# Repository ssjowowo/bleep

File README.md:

# Bleep

**A DIY touchscreen universal remote.** It's built around an ESP32-S3 on a main board of our own, with a 3.5″ IPS touch display, 14 physical keys, IR send and learn, haptics, and Home Assistant control over Wi-Fi. The case is 3D-printed and only 13 mm thick.

<p align="center">
  
  &nbsp;
  
</p>

## What it is

Most universal remotes either have a screen and few buttons, or lots of buttons and no screen. Bleep has both. The touchscreen shows activities, now-playing and smart-home controls. The keys you use without looking stay physical: a D-pad ring with OK, Back, Home, Mute, three app keys (YouTube, Netflix, Plex) and a volume rocker.

- **IR out**: two side-view 940 nm IR LEDs at the top end control TVs, receivers and boxes.
- **IR learning**: a 38 kHz receiver behind a small window under the screen copies codes from your old remotes.
- **Wi-Fi**: Home Assistant control of lights, scenes and media through the ESP32-S3.
- **Feel**: a coin vibration motor driven by a DRV2605L haptics driver.
- **Smart power**: lift-to-wake (accelerometer), wake on touch or any key, auto-brightness (light sensor), and a fuel gauge for an accurate battery percentage. Asleep it draws about 0.1–0.15 mA, so a charge lasts months.
- **USB-C** for charging and flashing.

The hardware is designed for all of this. The firmware's app and UI run today in an emulator (on the PC or in a browser) while the boards are being made; the ESP32-S3 port comes when they arrive. See [firmware/README.md](firmware/README.md).

The industrial design comes from a concept pack made in Claude Design (design **1b "Pebble"**, in `design/`). The brand (wordmark, logo lockup) comes from the Bleep brand book.

## Status

| Part | State |
|---|---|
| Main board v1 | **Ordered** from JLCPCB on 2026-10-08 (5 boards, 2 assembled). The design is locked: the files in `hardware/mainboard/` are the ones in production. |
| Enclosure | Ready to print. The back plate is flat, with room for a 4.0 × 50 × 85 mm Li-Po (405085) under the screen. |
| Display | BuyDisplay ER-TFT035IPS-6 + capacitive touch, **ordered** 2026-10-09. Its cable fold gets checked on the real panel before assembly. |
| Battery | **Ordered** 2026-10-09 (405085 planned; if the cell differs, set `BATT` in `layout.py` and rebuild the back plate). |
| Firmware | App and UI (C + LVGL 9) running in a PC/browser emulator with 32 scripted test scenarios; ESP-IDF port next. [firmware/](firmware/) |

## Hardware at a glance

| | |
|---|---|
| Size | 60.7 × 182.2 × 13.0 mm |
| MCU | ESP32-S3-WROOM-1-N8R2 (8 MB flash, 2 MB PSRAM), antenna at the right edge beside the D-pad |
| Display | 3.5″ IPS 320 × 480, ILI9488 on an 8-bit parallel bus (much faster than SPI), FT6236 capacitive touch |
| Keys | 14 tactile switches, each on its own wake-capable GPIO |
| IR | 2 × VSMB2948SL LEDs (≈ 125 mA peaks), IRM-H638T receiver for learning |
| Sensors | MMA8452Q accelerometer, LTR-303ALS light sensor, MAX17048 fuel gauge |
| Power | 1-cell Li-Po, TP4056 charger with load sharing, ME6211 3.3 V LDO |
| Board | 2 layers, 0.8 mm, 54 × 178 mm. JLCPCB assembles the top side; you solder the ESP32 module, battery and motor on the underside. |
| Case | PETG, two colours for the key labels (flush inlays), plus translucent blue PETG for the IR and sensor windows (two small separate prints); the board screwed to the front shell (4 × M2×4) and the back plate held by 2 × M2×8 and two snap fingers, all into heat-set inserts |

The parts list, pin map, assembly steps, ordering guide (≈ €130 in total, delivered to Cyprus) and firmware notes are in **[hardware/README.md](hardware/README.md)**.

## How it's built

Everything mechanical comes from one file, [`hardware/layout.py`](hardware/layout.py). It holds the display and part sizes, the key layout, where each part sits, the z stack and the screw points, and it runs fit checks on all of them. Two generators read it:

- **Enclosure**: `layout.py` writes `enclosure/params.scad`, and [`enclosure/remote.scad`](hardware/enclosure/remote.scad) (OpenSCAD) builds the front shell, its two windows, back plate, key caps and label inlays as STLs, plus interference checks.
- **Main board**: [`mainboard/gen_mainboard.py`](hardware/mainboard/gen_mainboard.py) places the parts in KiCad 10 from the same numbers. [Freerouting](https://github.com/freerouting/freerouting) routes it, then the generator adds ground pours, runs DRC and exports Gerbers, BOM and CPL for JLCPCB.

The board and the case can't drift apart. Since the board was ordered, `layout.py` checks every value the board was built from against `mainboard/pcb_lock.json`. It refuses to run if a case change would move one of them.

## Repository layout

```
design/              concept pack (open the .dc.html files in a browser), brand assets, outline drawings
hardware/
  layout.py          the single source of truth for the mechanics
  build.sh           rebuilds everything from layout.py
  enclosure/         OpenSCAD source and the printable STLs (enclosure/stl/)
  mainboard/         KiCad board, generator, routing logs; fab/ = Gerbers, BOM, CPL (locked)
  viewer/            3D colour viewer (three.js) for trying colourways
  docs/              datasheets and renders
HANDOFF.md           current working state, for picking the project up on another machine
```

## Building

```bash
cd hardware
./build.sh enclosure   # STLs, renders and fit checks
./build.sh viewer      # meshes for the 3D viewer (viewer/index.html)
```

You need Python 3 (no extra packages) and OpenSCAD 2021.01 or newer, on the PATH or set with `OPENSCAD=`. The board rebuild (`./build.sh pcb`) also needs KiCad 10 and Freerouting, and it's disabled while v1 is locked.

To open the 3D viewer locally, run `python3 -m http.server -d hardware/viewer 8742` and go to <http://localhost:8742>.

## Roadmap

1. Boards and display arrive: check the display cable fold, solder the underside parts, print the case.
2. Firmware: LVGL UI (activities, now playing, Home Assistant), IR send and learning through the RMT peripheral, deep sleep with key, touch and lift wake.
3. Fixes found on the real hardware go into a v2 board.

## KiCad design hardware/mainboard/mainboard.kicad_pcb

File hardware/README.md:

# Bleep v1 — hardware (own ESP32 + plug-in display)

**One main board of our own** with a **3.5" IPS panel with capacitive touch (BuyDisplay ER-TFT035IPS-6)** lying flat on it, plugged into a connector on the board. The keypad has a ring D-pad. The shell is slim: only wall and clearance beside the glass, the glass 4.8 mm from the top end (5 mm top corners), and the power key and sensor window in a row under the screen.

| | |
|---|---|
| Size | 60.7 × 182.2 × **13.0 mm** |
| Display | BuyDisplay ER-TFT035IPS-6 (ILI9488) + ER-TPC035-6 touch (FT6236), 3.75 mm, one 50-pin FPC |
| ESP32 | ESP32-S3-WROOM-1-N8R2 module (8 MB flash, 2 MB PSRAM) |
| Battery | flat Li-Po up to 4.0 mm thick and 50.8 × 86.1 mm (sized for a 405085), under the screen |
| You solder | ESP32 module, battery, vibration motor (the display just plugs in) |

Everything is generated from [`layout.py`](layout.py):

```bash
./build.sh            # everything: STLs, renders, PCB, viewer meshes
./build.sh enclosure  # STLs + renders + fit checks
./build.sh pcb        # main board: place, route, DRC, Gerbers, BOM/CPL
```

It needs Python 3 (no extra packages) and OpenSCAD 2021.01+, found on the PATH or set with `OPENSCAD=`. The PNG renders in `docs/` need a display, so on a headless Linux box they're skipped.

## Stack (from the back face, 4 mm cell)

| z (mm) | |
|---|---|
| 0 – 1.5 | back plate |
| 1.5 – 6.0 | open space: battery (+0.5 swell gap) under the screen; ESP32 module, vibration motor and the heads of the 4 board screws under the keys. The back plate is flat; the board rests on rails along its edges under the screen, a standoff at each of the plate's 2 screws and a 3 mm pillar under each key switch |
| 6.0 – 6.8 | main board, 0.8 mm |
| 6.8 – 8.4 | under the LCD: the 50-pin ZIF connector (1.5 mm), the folded display FPC and its parts area, foam pads at the top end |
| 8.4 – 12.15 | LCD (2.1) + touch glass (1.65) |
| 12.15 – 12.95 | front frame over the glass edge |

The cell thickness sets H: 3 mm → 12.0, 4 mm → 13.0, 5 mm → 14.0 mm. Change `BATT` in `layout.py` and rebuild.

## Main board

> **Locked (2026-10-08).** Bleep v1's main board is ordered from JLCPCB: 5 boards, green mask, HASL, Economic assembly of 2. `mainboard/mainboard.kicad_pcb` and `mainboard/fab/` are the ordered files and are read-only. `./build.sh` no longer touches the board, and `./build.sh pcb` refuses. Only the shell and the firmware change from here. `layout.py` stops with "PCB LOCKED" if a shell change would move anything the board was built from: part positions, keys, holes, outline, antenna keep-out, GPIO map. The record is in `mainboard/pcb_lock.json`.

Status (2026-10-08, slim version, after an independent review): fully routed, KiCad DRC **0 violations, 0 unconnected**; Gerbers, BOM and CPL in `mainboard/fab/`. The CPL rotations are checked against JLCPCB's own footprints for every part. Renders: [top](docs/mainboard-top.png), [underside](docs/mainboard-bottom.png).

Branding follows the Bleep Brand Book (PCB section): the logo lockup in one-colour silk, large on the back (40 mm, under the battery) and smaller on the front (26 mm, under the panel), each with the board ID `MAIN BOARD · V1 2026`. The display and the ring round the LED are knocked out of the silk, and both LED dots are bare copper pads. They come out gold with ENIG; with the HASL finish in the current order they're silver tin. The brand book also calls for a matte black solder mask; colour and finish are order options, not changes to the files. The lockup is built in `mainboard/logo.py` from the brand book's mark and a trace of the wordmark (`../design/brand/`); `gen_mainboard.py rebrand` re-applies it to the routed board without re-routing.

Routing: [Freerouting](https://github.com/freerouting/freerouting) 2.5 does it, about 5 minutes for `./build.sh pcb`. A few things are drawn by hand first and passed to it as fixed copper: the VSYS rail (charger → right edge → LDO → up the right side to the IR LEDs), the LDO's pins and the 3V3 run to the module, the vibration-motor wires (on the bottom layer) and the USB D+/D− crossing. VBAT and VSYS are 0.5–0.6 mm wide (the cell → LDO path carries the Wi-Fi bursts: ≈ 0.2 Ω end to end, about 0.1 V at 500 mA), the other power nets 0.3 mm, and Freerouting may not put vias in SMD pads. GND is a pour on both layers; after routing, `gen_mainboard.py fab` stitches any pour piece the tracks cut off back to the main ground with a via. Freerouting needs a Java 25 runtime; `build.sh` looks for it and the jar in `%LOCALAPPDATA%\freerouting\`, and its settings file (`%APPDATA%\freerouting\freerouting.json`) has automatic neck-down off, so no track goes below 0.15 mm. The older grid router (`mainboard/route.py`) is still there but couldn't route this layout.

| Part | Where | Notes |
|---|---|---|
| 14 key switches (TS-1187A) | top, JLCPCB | each straight to an ESP32 RTC GPIO, so any key wakes it |
| USB-C | top, bottom edge | 5.1 k CC pull-downs, D+/D− to the ESP32's native USB (flashing + serial) |
| TP4056 charger | top, right strip, near USB-C | 360 mA (PROG 3.3 k); CHRG/STDBY to GPIO12/3 |
| Load sharing (AO3401A + B5819W + 100 k) | top, under the charger | on USB the remote runs from VBUS and the charger sees only the cell, so it terminates properly; off USB the cell feeds the system through the P-MOSFET |
| ME6211 3.3 V LDO | top, over the module by its 3V3 pin | 500 mA, from VSYS (the cell, or USB when plugged in) |
| DRV2605L + MMA8452Q | top, left strip | haptics (always enabled, standby over I²C); accelerometer for lift-to-wake (INT1 → GPIO2, transient/motion interrupt) |
| 2 × VSMB2948SL IR LEDs | top edge, centred; their driver sits under the LCD | 22 Ω each from VSYS (≈ 125 mA peaks at 4.2 V), one AO3400A; silk arrows mark the lens direction |
| Backlight driver | top, right strip | LED+ from VSYS via 2 × 22 Ω (1206, they see up to ≈ 0.12 W each on USB), cathodes switched by an AO3400A on GPIO46 (PWM) |
| 50-pin 0.5 mm ZIF connector (XUNPU FPC-05F-50PH15) | top, under the panel, JLCPCB | bottom contact, flip lid; the display FPC folds under and plugs in |
| ESP32-S3-WROOM-1-N8R2 | **underside**, across the board just below the screen | **you solder**. It must be the **N8R2**: the N8R8 (octal PSRAM) uses GPIO35–37, which are LCD D0–D2 here; antenna at the **right edge**, beside the D-pad, with no copper on either layer around it (3.5 mm past the module's sides). It can't go under the screen: the panel would detune it. |
| IR receiver (Everlight IRM-H638T, 38 kHz) | in the row under the screen, left, under the sensor window (3.0 mm hole) | for **learning** codes from existing remotes; output on GPIO42. Powered from GPIO1 through 220 Ω + 10 µF, so it's only on while learning (it draws 0.4 mA) |
| Ambient light sensor (LTR-303ALS-01) | beside the IR receiver, same window (1.6 mm hole, with a translucent PETG light pipe down to it) | auto-brightness; I²C `0x29` |
| Fuel gauge (MAX17048) | top, left strip | battery %, time-to-empty and the cell voltage; I²C `0x36` |
| EN + GND reset pads | underside, below the module, under a slot in the back plate | short them (a small screwdriver across both) to reset the ESP32 without opening the case |
| BAT+ / BAT− pads, vibration-motor pads | underside: battery pads just below the screen on the left, motor in the left strip | the motor is an 8 mm ERM (or LRA) coin, set in firmware |

### ESP32-S3 pin map

| GPIO | Use | GPIO | Use |
|---|---|---|---|
| 0 | OK key (hold at reset = download mode) | 21 | LCD D/C |
| 1 | IR receiver power (high while learning) | 35 – 41 | LCD D0 – D6 |
| 2 | MMA8452Q INT1 (lift-to-wake) | 42 | IR receiver output (learning) |
| 3 | charger STDBY | 43 | LCD D7 |
| 4, 5, 6, 7 | UP, RIGHT, LEFT, DOWN | 44 | LCD WR |
| 8, 9 | NFLX, YT | 45 | IR LED (pulled low) |
| 10, 11 | VOL+, VOL− | 46 | backlight PWM (pulled low) |
| 12 | charger CHRG | 47, 48 | I²C SDA / SCL |
| 13, 14 | PWR key / touch INT | 19, 20 | USB D− / D+ |
| 15, 16, 17, 18 | BACK, HOME, MUTE, PLEX | | |

I²C: FT6236 touch `0x38`, DRV2605L `0x5A`, MMA8452Q `0x1C`, LTR-303ALS `0x29`, MAX17048 `0x36`. The LCD and touch controller share an RC power-on reset (10 k × 1 µF), so after power-up the firmware resets the ILI9488 with its software-reset command (0x01). Display: ILI9488 on the ESP32-S3's i80 LCD bus, **8080 8-bit parallel** (IM2–IM0 = 011, CS tied low, RD tied high), 320 × 480. That's several times faster than the ILI9488's SPI mode, which only takes 18-bit colour. GPIO43/44 are UART0, so use the USB-Serial/JTAG console in firmware; the ROM's boot messages on GPIO43 are harmless because WR stays high. Every GPIO is used.

## Display

**BuyDisplay ER-TFT035IPS-6** — 3.5" IPS, 320 × 480, ILI9488, LCD 54.56 × 82.84 × 2.1 mm — with the **ER-TPC035-6** capacitive touch panel (FT6236, glass 56.54 × 84.96 mm, 3.75 mm in total). Backlight ≈ 3.0–3.3 V at 120 mA. One 50-pin 0.5 mm FPC, 30 mm long, carries the LCD and the touch I²C. The datasheet, touch drawing and connector drawing are in `docs/`; the old QD3525 papers are in `docs/old-qd3525/`.

The FPC leaves the panel's bottom edge, makes a U-bend down past the glass and runs 24 mm back under the LCD into the ZIF connector J1. That puts the FPC's pin 1 on the right, seen from the front; the board's silk says so. The FPC's small parts area (≤ 1.5 mm) also lies under the LCD.

## Assembly order

1. **ESP32 module** (underside, lying across the board below the screen, antenna end at the right edge as the silk shows): tack two corners, then solder the edge pads. Solder the centre GND pad from the top side: feed solder into its four 1 mm holes until each one fills (the module's pad heats slowly, so use a hot, broad tip). Pins 1 and 40 (GND, by the antenna) are also tied to that pad with tracks.
2. **Battery** leads to BAT+ / BAT− (underside, just below the screen on the left), **motor** leads to its pads (red to +). Cut the battery's plug off and solder the leads straight to the pads, red to BAT+: at 4 mm there's no room for a connector. Stick the motor to the board's underside by its adhesive back, on its spot in the left strip. The cell goes at the top end, under the screen and as far from the antenna as it goes, between the four corner guides on the back plate; its leads run down to the pads. A piece of Kapton tape on the board's underside over the cell area keeps via tips off the pouch.
3. **Display**: lay the panel face down beyond the board's key end, FPC towards J1. Flip J1's lid up, slide the FPC in with its contacts facing the board, then close the lid. Fold the panel over onto foam pads (two layers of 1 mm foam tape) at the board's top end, so the FPC makes a U-bend under it. Stick the pads left and right of the small IR-driver parts there (they sit under the LCD now), not on them.
4. Flash over USB-C. esptool resets the ESP32 into download mode over USB by itself. If a broken firmware stops that from working, hold OK and short the two reset pads through the slot in the back plate (a small flat screwdriver across both), then release them while still holding OK. Plugging in USB doesn't reset the ESP32 once the battery is connected.
5. Key caps into the front shell, face down: the **OK** button first, then the one-piece **D-pad ring** over it (the ring holds the OK in), then the other caps.
6. Board into the front shell (glass into its pocket), then screw it to the four posts in the key area with **4 × M2×4** from its underside, into the inserts. Use nylon screws, or at least put a disc of Kapton tape under the head at the top-left hole (H1): a VBAT track passes 1.75 mm from its centre on the underside, under the edge of a 4 mm head, with only solder mask in between.
7. Battery on the back plate between its corner guides. Hook the back plate's top end in first: its two snap fingers click into grooves in the top wall. Then close it with **2 × M2×8** through the bottom bosses (they pass through the board too).

## Ordering

Prices checked 2026-10-07, delivered to Cyprus. Every AliExpress line adds about €3 of EU import charges.

### 1. JLCPCB: PCB + assembly, plus LCSC in the same parcel

Before paying, open J1 in the Component Placements 3D view: its flip lid and opening must face the bottom of the board (towards the keys), where the folded cable comes from. Upload `mainboard/fab/mainboard-gerbers.zip`, then PCB Assembly with `mainboard-BOM.csv` and `mainboard-CPL.csv`. PCB: 2 layers, **0.8 mm**, HASL, qty 5. Assembly: **Economic**, top side, qty 2. Order remark for the IR LEDs: *"D1/D2 VSMB2948SL side-view IR LEDs: lens faces the board's top edge (silk arrows), cathode = pad marked K."*

| JLCPCB item | US$ |
|---|---|
| 5 PCBs, 2 layers, 0.8 mm, 54 × 178 mm | ≈ 9.40 |
| Economic assembly setup + stencil | ≈ 9.71 |
| 10 Extended parts × $3.07 (USB-C, TP4056, ME6211, DRV2605L, MMA8452Q, IR LED, ZIF connector, IR receiver, light sensor, fuel gauge) | 30.70 |
| Parts for 2 boards (DRV2605L $1.58, MMA8452Q $1.57, MAX17048 $1.31, IR LED $0.45, LTR-303ALS $0.27, ZIF $0.21, IR receiver $0.13, TP4056 $0.18, AO3400A $0.09, USB-C $0.07, ME6211 $0.06, switches $0.02 …) | ≈ 15.00 |
| Solder joints | ≈ 1.20 |
| **JLCPCB subtotal** | **≈ 66** |

Then at [LCSC](https://www.lcsc.com/) add these and choose "Combine your LCSC and JLCPCB orders" at checkout (one parcel, one shipping fee):

| Part | LCSC | Qty | US$ |
|---|---|---|---|
| ESP32-S3-WROOM-1-N8R2 | [C2913204](https://www.lcsc.com/product-detail/C2913204.html) | 2 (one spare) | 9.36 |
| M2 × 3 × 3.2 brass heat-set insert | [C51938982](https://www.lcsc.com/product-detail/C51938982.html) | 50 (minimum) | 0.50 |

Shipping ≈ $11 (Global Standard, 12–19 days). VAT is added at checkout.

### 2. BuyDisplay: the display

[3.5" IPS 320×480 TFT with capacitive touch](https://www.buydisplay.com/3-5-inch-ips-320x480-tft-lcd-display-capacitive-touch-screen) (ER-TFT035IPS-6). Options:

- **"3.5" Capacitive Touch Panel with Controller"** (+$5.57)

≈ US$15.20 + ≈ $10 shipping. Expect Cyprus VAT (19 %) and maybe a courier handling fee on delivery. The price and options come from an archived copy of the page (the live site has a bot check), so confirm them at checkout.

### 3. AliExpress (Ship to: Cyprus)

| Part | Listing | Variant | € |
|---|---|---|---|
| 8 mm coin vibration motor, ERM 0827, 5 pcs | [1005007600971536](https://www.aliexpress.com/item/1005007600971536.html) | "8x2.7mm" | 2.24 |
| M2 × 8 pan-head screws, 100 pcs | [1005005581270091](https://www.aliexpress.com/item/1005005581270091.html) | "M2 100pcs" + "8mm" | 2.99 |
| M2 × 4 nylon pan-head screws (the board screws) | search "M2 nylon screw 4mm" | 4 mm | ≈ 1–2 |
| 1 mm double-sided foam tape, 10 m | [1005007483857645](https://www.aliexpress.com/item/1005007483857645.html) | 10 mm wide | 3.53 |

Alternative screws: [4000970993800](https://www.aliexpress.com/item/4000970993800.html) (€2.26, 50 pcs stainless). An LRA 0832 exists ([1005010354264566](https://www.aliexpress.com/item/1005010354264566.html)) but costs ≈ €23.6 with shipping; the ERM works with the DRV2605L (a firmware setting).

### 4. Battery: Eremit, to the German forwarding address

Li-Po cells count as dangerous goods for shipping, and the shops that sell them won't send them to Cyprus directly. Eremit ships only within Germany but explicitly allows forwarding services, so order to the forwarder's German address.

Look for a flat Li-Po (pouch) cell, **at most 4.0 mm thick and 50.8 × 86.1 mm**, with its leads on a short edge and a protection circuit. Pouch cells are named by size: thickness in tenths of a mm, then width, then length, so **405085** is 4.0 × 50 × 85 mm, the largest that fits and the one the back plate is set up for. 3.0–4.0 mm thick, up to 50 mm wide and 86 mm long all fit: 405085, 405080, 404080, 405060 or the smaller 404060. Set `BATT` in `layout.py` to the cell you buy and rebuild the back plate, so its corner guides fit it. Not yet chosen.

### Rough total

| | € |
|---|---|
| JLCPCB + LCSC + shipping (≈ US$86) | ≈ 74 + VAT |
| BuyDisplay panel + touch + shipping (≈ US$25) | ≈ 22 + VAT |
| AliExpress (3 lines) + ≈ €9 import charges | ≈ 17.80 |
| Batteries (to Germany, not yet chosen) | ≈ 15–20 + forwarding |
| **Total** | **≈ €130 + forwarding + VAT on the JLCPCB and BuyDisplay parts** |

Already on hand (not counted): PETG in two colours, solder, flux, solder wick. The second colour prints the key labels and the ring dots.

**Windows.** The IR window and the sensor window are two small separate prints in translucent PETG (Creality CR-PETG Translucent Blue), fitted by hand with a drop of clear glue:

- `stl/ir_window.stl` (15.8 × 6.2 × 1.8 mm, printed flange down): a plug that fills the slot in the top wall, flush outside. Push it in from the inside before the board goes in; its flange sits in the recess round the slot, so it can't be pushed out.
- `stl/sensor_window.stl` (10.8 × 3.8 mm, pegs 4.95 mm tall, printed pill face down): the pill sits flush in its recess under the screen, with a peg down through each hole. The peg over the light sensor runs on to 0.5 mm above it as a light pipe, because through the bare 1.6 mm hole the sensor would see only about ±8°.

Each has 0.1 mm clearance per side for a press fit; if a peg is too tight, run a 1.5 / 3.0 mm drill through the shell's holes. Print a few spares: they're tiny.

Before printing the real ones, check the filament passes infrared. Print a 1 mm square, hold it over a working remote's LED and work your TV from across the room (a phone's front camera usually shows the LED's glow through it too). Clear and translucent dyed PETG normally pass 940 nm. The blue tint dims and colours what the light sensor sees, so its lux reading needs a scale factor in firmware; calibrate it once against a phone's light meter. Auto-brightness only needs it to rise and fall with the room.

## The display cable fold

The board is designed from BuyDisplay's drawings, and the cable fold is the one thing the drawings can't settle. The cable leaves the panel through two narrow, flexible necks only 3.9 mm long. After them comes a 48 mm wide section, centred about 2.4 mm towards pin 1 (right), with a strip of parts 4.9–7.0 mm out from the glass edge. How much cable the real fold uses can't be predicted to better than about ±1.5 mm. So the design has slack:

- J1 sits 1.6 mm closer to the fold than the nominal fold needs. A looser fold still reaches fully into J1. A tighter one bottoms out in J1, and the extra cable makes the fold bulge outward by about half of it.
- The enclosure model uses the full 48 mm width for the fold, already bulged, and keeps it clear of the power key, the IR receiver, the UP switch and the antenna.

Ordering the display and the boards together is fine. When the display arrives, check the fold before assembling: lay the panel face down beyond the key end, fold the cable under as it will sit, and hold the panel in place. The cable end should slide fully into J1, and the fold shouldn't stick out more than about 2 mm past the glass edge. If either is off, the fix goes in the 3D-printed front shell, not the board: the glass pocket moves by up to about ±1 mm towards or away from the fold, and you reprint the front shell. Ask me for that change. `LENS_Y0` in `layout.py` also positions J1, so it has to be done with J1 pinned to where it is on the boards you have.

## Firmware notes

- IR: send with a 33 % carrier duty (the LEDs see ≈ 125 mA peaks).
- Backlight: it's fed from VSYS through 11 Ω. On battery it dims as the cell drains (≈ 100 mA at 4.2 V, much less near 3.4 V), so scale the PWM duty with the measured battery voltage. On USB, VSYS is ≈ 4.6 V and full duty would be ≈ 135 mA, above the panel's 120 mA rating. Cap the duty at about 85 % while USB is present, which is when CHRG (GPIO12) or STDBY (GPIO3) reads low.
- Charger status: CHRG (GPIO12) and STDBY (GPIO3) are open-drain and have no pull-ups on the board, so enable the ESP32's internal pull-ups on both. Both are RTC GPIOs, so use `rtc_gpio_pullup_en()` for them in deep sleep. Read them as:
  - CHRG low = charging
  - STDBY low = full
  - both high = no USB
- Lift-to-wake: ignore MMA8452Q interrupts while the vibration motor runs; it's ~7 mm away.
- IR learning: drive GPIO1 high to power the receiver and wait about 100 ms for it to settle, then capture GPIO42 with the RMT peripheral in receive mode (the output is active-low and demodulated). Turn the IR LEDs off while learning. Afterwards drive GPIO1 low and keep GPIO42's pull-up off, so nothing powers the receiver through its output; hold GPIO1 low in deep sleep (`rtc_gpio_hold_en()`).
- Light sensor: it looks out through a 1.6 mm hole about 5 mm above it, so treat its readings as relative and calibrate the brightness curve by eye.
- Fuel gauge: read SOC (register 0x04), CRATE and VCELL (0x02, the cell voltage, also used for the backlight scaling); it runs straight off the cell and needs no setup beyond an optional quick-start. Let it hibernate in standby (≈ 4 µA instead of 23 µA).
- Standby budget: with the IR receiver off, the board draws roughly 0.1–0.15 mA asleep (the ESP32 in deep sleep, the LDO's 40 µA, the touch controller in monitor mode, the accelerometer and the fuel gauge), so a 1000 mAh cell lasts several months.
- Touch sleep: the FT6236's reset is on the RC power-on reset, not a GPIO, and it only leaves hibernate through a reset. So never send it to hibernate; use its monitor mode, which wake-on-touch (GPIO14) needs anyway.
- Haptics and Wi-Fi share the 3.3 V regulator (500 mA). A Wi-Fi transmit burst (≈ 350 mA) plus the motor (up to ≈ 100 mA) is close to its limit on a nearly empty cell, so keep haptic pulses short and fire them just after the Home Assistant request has gone out, not during it.
- Near an empty cell (≈ 3.4 V) the backlight has almost no headroom over the LEDs' 3.0–3.2 V and gets very dim; that's expected.

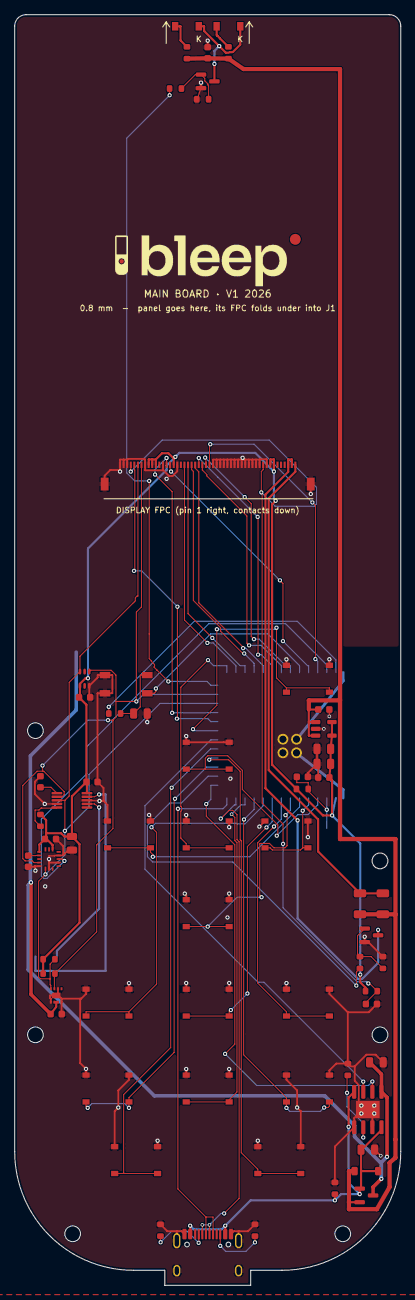
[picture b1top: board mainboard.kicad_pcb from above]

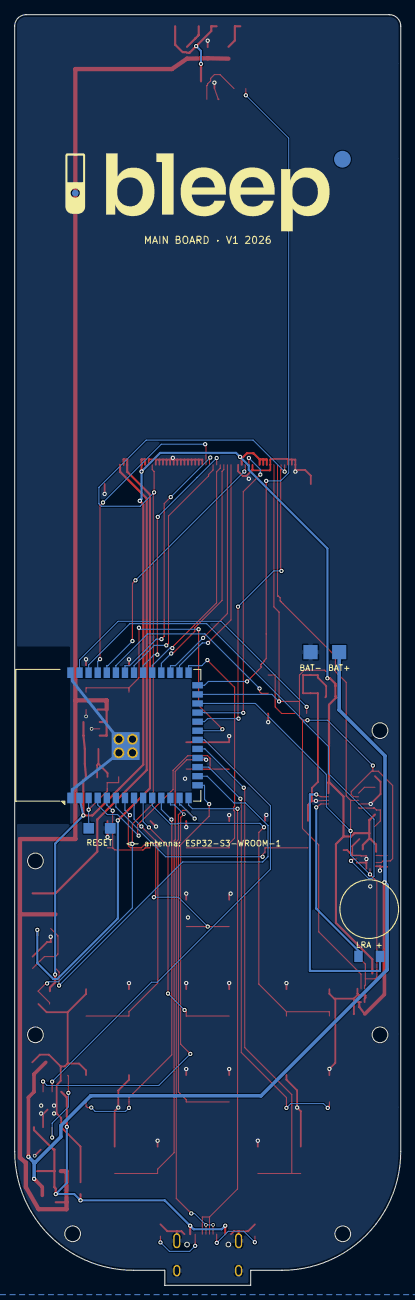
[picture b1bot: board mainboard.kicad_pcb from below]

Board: 2 copper layers, 53.9 x 177.5 mm, 80 parts (8 on the bottom side), 59 nets.

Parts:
C1: 22uF; C_0805_2012Metric
C2, C9, C13: 100nF; C_0603_1608Metric
C3, C4, C7, C8, C15, C17, C18: 1uF; C_0603_1608Metric
C5, C11, C12, C14, C16: 10uF; C_0805_2012Metric
C6: 10uF; C_0603_1608Metric
D1, D2: VSMB2948SL; VSMB2948SL_SideView
D3: B5819W; D_SOD-123
H1, H2, H3, H4, H5, H6: M2; MountingHole_2.2mm_M2
J1: FPC-05F-50PH15
J3: TYPE-C 16PIN 2MD(073); USB_C_Receptacle_HRO_TYPE-C-31-M-12
LOGO_BACK1, LOGO_BACK2: logo LED dot
LOGO_FRONT1, LOGO_FRONT2: logo LED dot
M1: LRA 0832 (8 mm coin, wired); LRA_8mm_WirePads
Q1, Q2: AO3400A; SOT-23
Q3: AO3401A; SOT-23
R1, R10: 10k; R_0603_1608Metric
R2, R3: 22R; R_0603_1608Metric
R4, R8: 100R; R_0603_1608Metric
R5, R9, R11, R19: 100k; R_0603_1608Metric
R6, R7: 22R; R_1206_3216Metric
R12, R13: 4.7k; R_0603_1608Metric
R16: 3.3k; R_0603_1608Metric
R17, R18: 5.1k; R_0603_1608Metric
R20: 220R; R_0603_1608Metric
SW1, SW2, SW3, SW4, SW5, SW6, SW7, SW8, SW9, SW10, SW11, SW12, SW13, SW14: TS-1187A-B-A-B; SW_Push_1P1T_XKB_TS-1187A
TP1, TP2: battery lead pad; TestPoint_Pad_2.0x2.0mm
TP3, TP4: reset pad; TestPoint_Pad_1.5x1.5mm
U1: ESP32-S3-WROOM-1-N8R2; ESP32-S3-WROOM-1
U2: ME6211C33M5G-N; SOT-23-5
U3: DRV2605LDGST; MSOP-10_3x3mm_P0.5mm
U4: MMA8452QR1; MMA8452Q_QFN-16_3x3mm_P0.5mm
U5: TP4056; SOIC-8-1EP_3.9x4.9mm_P1.27mm_EP2.41x3.3mm
U6: IRM-H638T/TR2; IRM-H638T
U7: LTR-303ALS-01
U8: MAX17048G+T10; MAX17048_TDFN-8_2x2mm

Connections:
3V3: C1.2, C2.2, C5.2, C8.1, C9.1, C14.2, C17.1, J1.9, J1.10, J1.11, J1.16, J1.43, J1.44, R1.1, R10.1, R11.2, R12.1, R13.1, U1.2, U2.4, U2.5, U3.10, U4.1, U4.14, U7.1
ACC_BYP: C13.2, U4.2
ACC_INT: U1.38, U4.11
BL_A: J1.50, R6.2, R7.2
BL_G: Q2.1, R8.2, R9.1
BL_K: J1.48, J1.49, Q2.3
BL_PWM: R8.1, U1.16
CC1: J3.A5, R17.1
CC2: J3.B5, R18.1
CHRG: U1.20, U5.7
DRV_EN: R11.1, U3.5
DRV_REG: C7.1, U3.1
EN: C3.1, R1.2, TP3.1, U1.3
GND: C1.1, C2.1, C3.2, C4.2, C5.1, C6.2, C7.2, C8.2, C9.2, C11.2, C12.2, C13.1, C14.1, C15.2, C16.2, C17.2, C18.2, J1.1, J1.2, J1.3, J1.8, J1.13, J1.17, J1.27, J1.28, J1.29, J1.30, J1.31, J1.32, J1.33, J1.34, J1.35, J1.36, J1.37, J1.38, J1.39, J1.40, J1.42, J1.51, J1.52, J3.A1, J3.A12, J3.B1, J3.B12, J3.SH, Q1.2, Q2.2, R5.1, R9.2, R16.2, R17.2, R18.2, R19.2, SW1.1, SW2.1, SW3.1, SW4.1, SW5.1, SW6.1, SW7.1, SW8.1, SW9.1, SW10.1, SW11.1, SW12.1, SW13.1, SW14.1, TP2.1, TP4.1, U1.1, U1.40, U1.41, U2.2, U3.4, U3.8, U4.5, U4.7, U4.10, U4.12, U5.1, U5.3, U5.9, U6.1, U6.2, U7.3, U8.1, U8.4, U8.6, U8.9
IRRX_PWR: R20.1, U1.39
IRRX_V: C16.1, R20.2, U6.4
IR_G: Q1.1, R4.2, R5.2
IR_RX: U1.35, U6.3
IR_TX: R4.1, U1.26
K_BACK: SW6.2, U1.8
K_DOWN: SW5.2, U1.7
K_HOME: SW7.2, U1.9
K_LEFT: SW4.2, U1.6
K_MUTE: SW8.2, U1.10
K_NFLX: SW10.2, U1.12
K_OK: SW3.2, U1.27
K_PLEX: SW9.2, U1.11
K_PWR: SW14.2, U1.21
K_RIGHT: SW2.2, U1.5
K_UP: SW1.2, U1.4
K_VOLDN: SW13.2, U1.19
K_VOLUP: SW12.2, U1.18
K_YT: SW11.2, U1.17
LCD_D0: J1.19, U1.28
LCD_D1: J1.20, U1.29
LCD_D2: J1.21, U1.30
LCD_D3: J1.22, U1.31
LCD_D4: J1.23, U1.32
LCD_D5: J1.24, U1.33
LCD_D6: J1.25, U1.34
LCD_D7: J1.26, U1.37
LCD_DC: J1.14, U1.23
LCD_RST: C15.1, J1.4, J1.41, R10.2
LCD_WR: J1.15, U1.36
LED1_A: D1.2, R2.2
LED2_A: D2.2, R3.2
LED_K: D1.1, D2.1, Q1.3
MOT_N: M1.2, U3.9
MOT_P: M1.1, U3.7
PROG: R16.1, U5.2
SCL: J1.7, R13.2, U1.25, U3.2, U4.4, U7.4, U8.7
SDA: J1.6, R12.2, U1.24, U3.3, U4.6, U7.6, U8.8
STDBY: U1.15, U5.6
TP_INT: J1.5, U1.22
USB_DN: J3.A7, J3.B7, U1.13
USB_DP: J3.A6, J3.B6, U1.14
VBAT: C12.1, C18.1, Q3.3, TP1.1, U5.5, U8.2, U8.3
VBUS: C11.1, D3.2, J3.A4, J3.A9, J3.B4, J3.B9, Q3.1, R19.1, U5.4, U5.8
VSYS: C4.1, C6.1, D3.1, Q3.2, R2.1, R3.1, R6.1, R7.1, U2.1, U2.3

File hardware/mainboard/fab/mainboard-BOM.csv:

Comment,Designator,Footprint,LCSC Part #
100R,"R4,R8",R_0603_1608Metric,C22775
100k,"R5,R9,R11,R19",R_0603_1608Metric,C25803
100nF,"C2,C9,C13",C_0603_1608Metric,C14663
10k,"R1,R10",R_0603_1608Metric,C25804
10uF,C6,C_0603_1608Metric,C19702
10uF,"C5,C11,C12,C14,C16",C_0805_2012Metric,C15850
1uF,"C3,C4,C7,C8,C15,C17,C18",C_0603_1608Metric,C15849
220R,R20,R_0603_1608Metric,C22962
22R,"R2,R3",R_0603_1608Metric,C23345
22R,"R6,R7",R_1206_3216Metric,C17958
22uF,C1,C_0805_2012Metric,C45783
3.3k,R16,R_0603_1608Metric,C22978
4.7k,"R12,R13",R_0603_1608Metric,C23162
5.1k,"R17,R18",R_0603_1608Metric,C23186
AO3400A,"Q1,Q2",SOT-23,C20917
AO3401A,Q3,SOT-23,C15127
B5819W,D3,D_SOD-123,C8598
DRV2605LDGST,U3,MSOP-10_3x3mm_P0.5mm,C425927
FPC-05F-50PH15,J1,FPC-05F-50PH15,C2856826
IRM-H638T/TR2,U6,IRM-H638T,C91447
LTR-303ALS-01,U7,LTR-303ALS-01,C364577
MAX17048G+T10,U8,MAX17048_TDFN-8_2x2mm,C2682616
ME6211C33M5G-N,U2,SOT-23-5,C82942
MMA8452QR1,U4,MMA8452Q_QFN-16_3x3mm_P0.5mm,C11360
TP4056,U5,SOIC-8-1EP_3.9x4.9mm_P1.27mm_EP2.41x3.3mm,C16581
TS-1187A-B-A-B,"SW1,SW2,SW3,SW4,SW5,SW6,SW7,SW8,SW9,SW10,SW11,SW12,SW13,SW14",SW_Push_1P1T_XKB_TS-1187A,C318884
TYPE-C 16PIN 2MD(073),J3,USB_C_Receptacle_HRO_TYPE-C-31-M-12,C2765186
VSMB2948SL,"D1,D2",VSMB2948SL_SideView,C6604342
